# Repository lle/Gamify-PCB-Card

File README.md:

# Version 3: Added new game mode
## Change Logs
* Denser LED matrix
* Added Racing Game (hold "A" when powering on)
* Added LED animation/screensaver (hold "B" when powering on)
* Updated silkscreen and contact information

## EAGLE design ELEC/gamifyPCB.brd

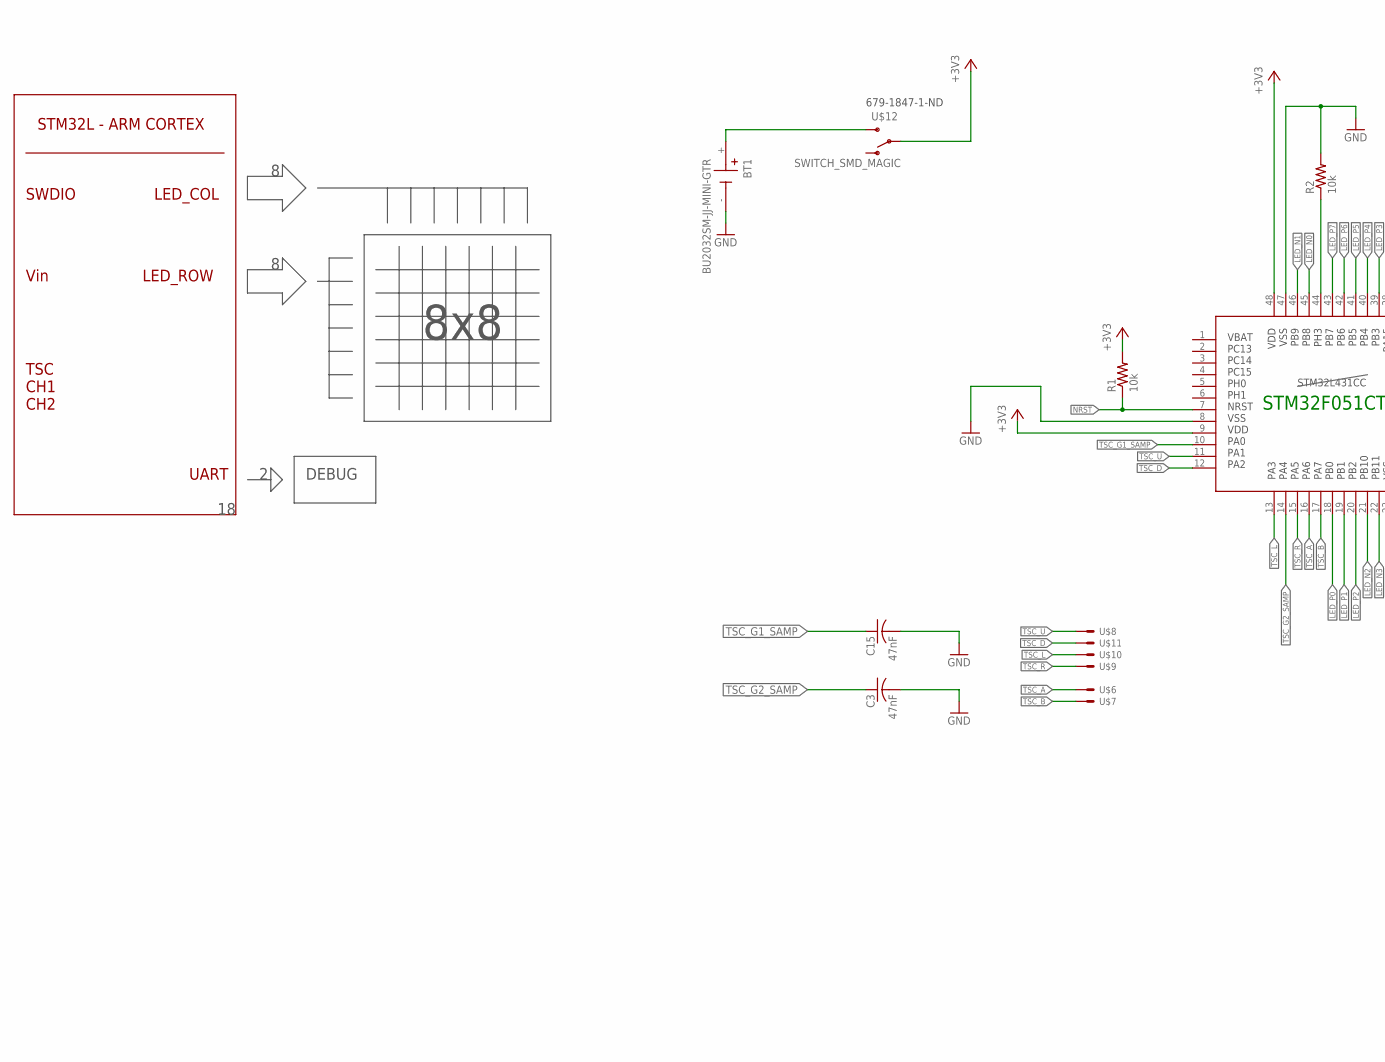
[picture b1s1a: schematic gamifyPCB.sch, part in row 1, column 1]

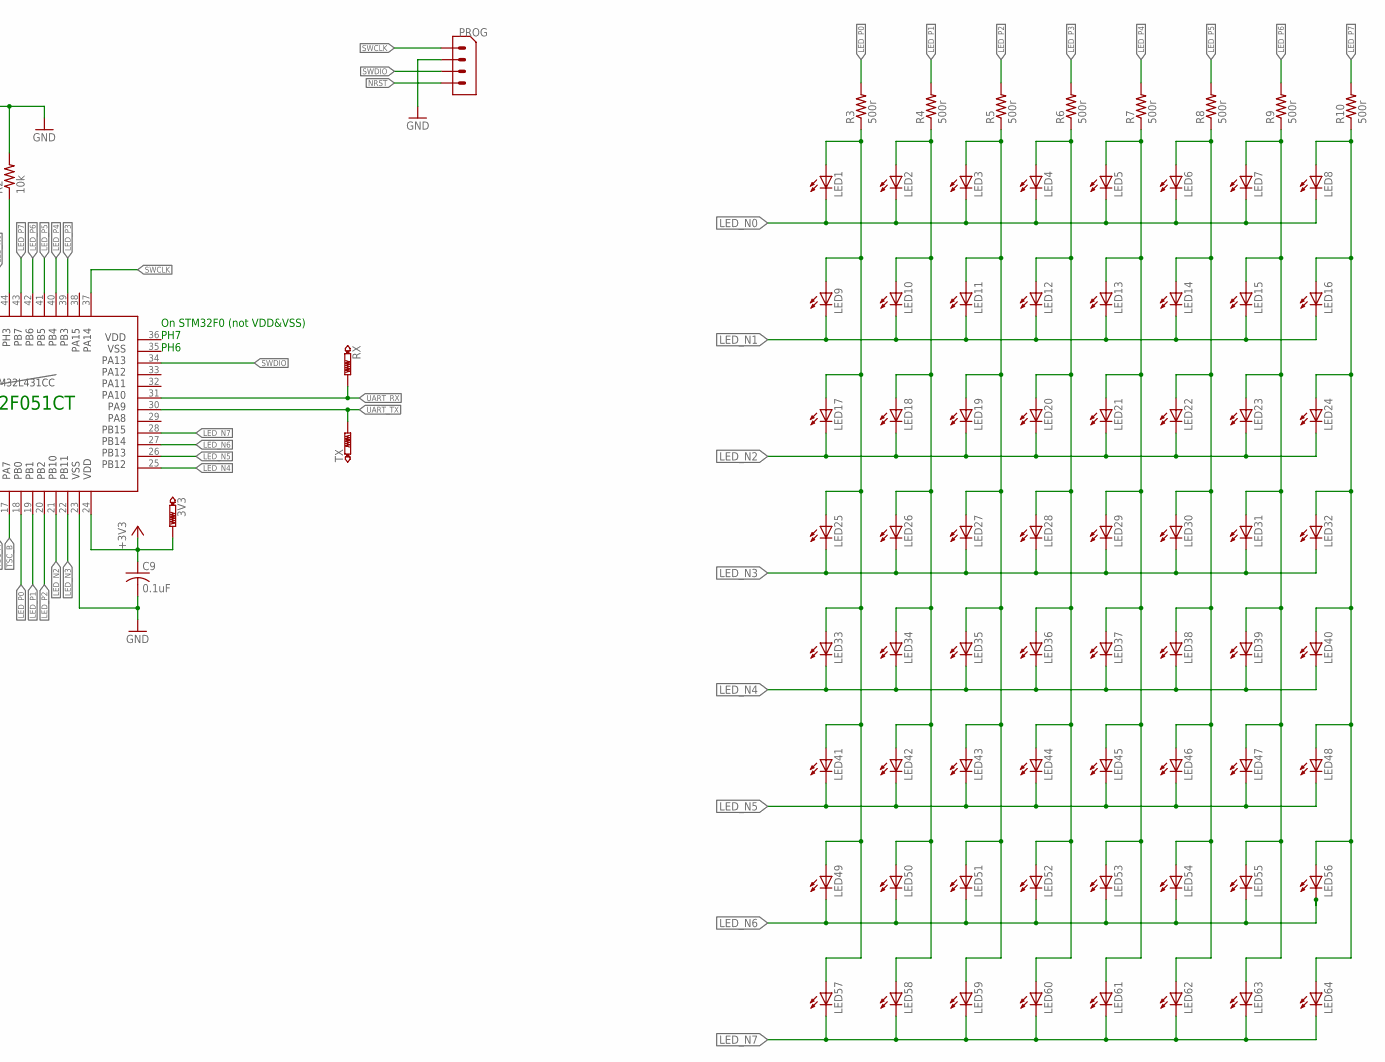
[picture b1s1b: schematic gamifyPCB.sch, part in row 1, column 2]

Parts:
3V3: PTR1B1,27; B1,27
BT1: BU2032SM-JJ-MINI-GTR; BAT_BU2032SM-JJ-MINI-GTR
C3, C15: 47nF; C0603
C9: 0.1uF; C0603
LED1, LED2, LED3, LED4, LED5, LED6, LED7, LED8, LED9, LED10, LED11, LED12, LED13, LED14, LED15, LED16, LED17, LED18, LED19, LED20, LED21, LED22, LED23, LED24, LED25, LED26, LED27, LED28, LED29, LED30, LED31, LED32, LED33, LED34, LED35, LED36, LED37, LED38, LED39, LED40, LED41, LED42, LED43, LED44, LED45, LED46, LED47, LED48, LED49, LED50, LED51, LED52, LED53, LED54, LED55, LED56, LED57, LED58, LED59, LED60, LED61, LED62, LED63, LED64: LEDCHIP-LED0603; CHIP-LED0603
PROG: 4-PIN-1.25MM
R1, R2: 10k; R0603
R3, R4, R5, R6, R7, R8, R9, R10: 500r; R0603
RX: PTR1B1,27; B1,27
TX: PTR1B1,27; B1,27
U$2: STM32L431CC; QFP50P900X900X160-48
U$6, U$7: CAP_BUTTON; CAPBUTTON
U$8, U$9, U$10, U$11: CAP_DPAD; DPAD
U$12: SWITCH_SMD_MAGIC; SWITCH_SMD_SUNKEN

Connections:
+3V3: 3V3.TP, C9.1, R1.2, U$2.9, U$2.24, U$2.48, U$12.2
GND: BT1.-, C3.2, C9.2, C15.2, PROG.P$3 (2), R2.2, U$2.8, U$2.23, U$2.47
LED_N0: LED1.C, LED2.C, LED3.C, LED4.C, LED5.C, LED6.C, LED7.C, LED8.C, U$2.45
LED_N1: LED9.C, LED10.C, LED11.C, LED12.C, LED13.C, LED14.C, LED15.C, LED16.C, U$2.46
LED_N2: LED17.C, LED18.C, LED19.C, LED20.C, LED21.C, LED22.C, LED23.C, LED24.C, U$2.21
LED_N3: LED25.C, LED26.C, LED27.C, LED28.C, LED29.C, LED30.C, LED31.C, LED32.C, U$2.22
LED_N4: LED33.C, LED34.C, LED35.C, LED36.C, LED37.C, LED38.C, LED39.C, LED40.C, U$2.25
LED_N5: LED41.C, LED42.C, LED43.C, LED44.C, LED45.C, LED46.C, LED47.C, LED48.C, U$2.26
LED_N6: LED49.C, LED50.C, LED51.C, LED52.C, LED53.C, LED54.C, LED55.C, LED56.C, U$2.27
LED_N7: LED57.C, LED58.C, LED59.C, LED60.C, LED61.C, LED62.C, LED63.C, LED64.C, U$2.28
LED_P0: R3.2, U$2.18
LED_P0B: LED1.A, LED9.A, LED17.A, LED25.A, LED33.A, LED41.A, LED49.A, LED57.A, R3.1
LED_P1: R4.2, U$2.19
LED_P1B: LED2.A, LED10.A, LED18.A, LED26.A, LED34.A, LED42.A, LED50.A, LED58.A, R4.1
LED_P2: R5.2, U$2.20
LED_P2B: LED3.A, LED11.A, LED19.A, LED27.A, LED35.A, LED43.A, LED51.A, LED59.A, R5.1
LED_P3: R6.2, U$2.39
LED_P3B: LED4.A, LED12.A, LED20.A, LED28.A, LED36.A, LED44.A, LED52.A, LED60.A, R6.1
LED_P4: R7.2, U$2.40
LED_P4B: LED5.A, LED13.A, LED21.A, LED29.A, LED37.A, LED45.A, LED53.A, LED61.A, R7.1
LED_P5: R8.2, U$2.41
LED_P5B: LED6.A, LED14.A, LED22.A, LED30.A, LED38.A, LED46.A, LED54.A, LED62.A, R8.1
LED_P6: R9.2, U$2.42
LED_P6B: LED7.A, LED15.A, LED23.A, LED31.A, LED39.A, LED47.A, LED55.A, LED63.A, R9.1
LED_P7: R10.2, U$2.43
LED_P7B: LED8.A, LED16.A, LED24.A, LED32.A, LED40.A, LED48.A, LED56.A, LED64.A, R10.1
unnamed: R2.1, U$2.44
unnamed: BT1.+, U$12.3 (S)
NRST: PROG.P$1 (4), R1.1, U$2.7
SWCLK: PROG.P$4 (1), U$2.37
SWDIO: PROG.P$2 (3), U$2.34
TSC_A: U$2.16, U$6.P$1, U$6.P$2
TSC_B: U$2.17, U$7.P$1, U$7.P$2
TSC_D: U$2.12, U$11.P$1
TSC_G1_SAMP: C15.1, U$2.10
TSC_G2_SAMP: C3.1, U$2.14
TSC_L: U$2.13, U$10.P$1
TSC_R: U$2.15, U$9.P$1
TSC_U: U$2.11, U$8.P$1
UART_RX: RX.TP, U$2.31
UART_TX: TX.TP, U$2.30

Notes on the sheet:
SWDIO
Vin
LED_COL
LED_ROW
TSC CH1 CH2
STM32L - ARM CORTEX
DEBUG
UART
8x8
679-1847-1-ND
STM32F051CT
On STM32F0 (not VDD&VSS) PH7 PH6

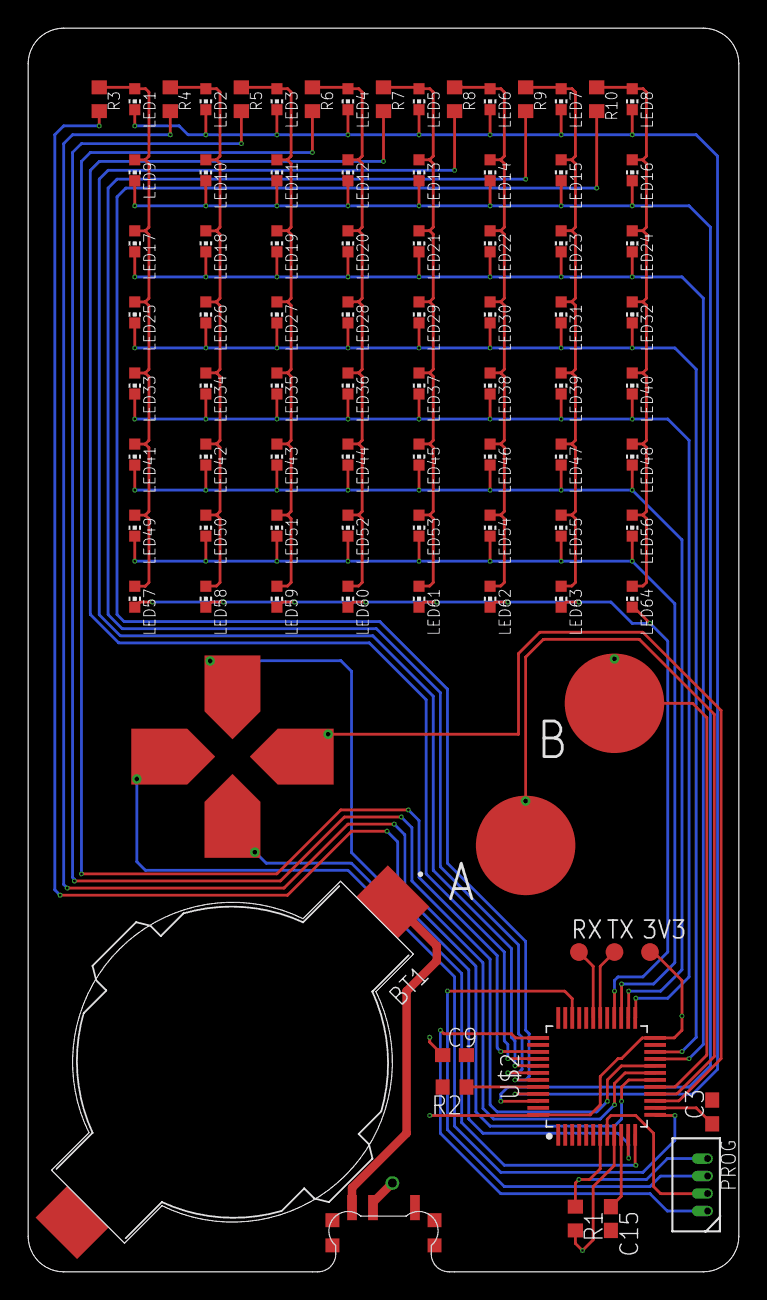
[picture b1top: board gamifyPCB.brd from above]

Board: 2 copper layers, 50.8 x 88.9 mm, 90 parts (0 on the bottom side), 41 nets.

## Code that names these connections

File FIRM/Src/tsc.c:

/**
  ******************************************************************************
  * File Name          : TSC.c
  * Description        : This file provides code for the configuration
  *                      of the TSC instances.
  ******************************************************************************
  * @attention
  *
  * <h2><center>&copy; Copyright (c) 2020 STMicroelectronics.
  * All rights reserved.</center></h2>
  *
  * This software component is licensed by ST under BSD 3-Clause license,
  * the "License"; You may not use this file except in compliance with the
  * License. You may obtain a copy of the License at:
  *                        opensource.org/licenses/BSD-3-Clause
  *
  ******************************************************************************
  */

/* Includes ------------------------------------------------------------------*/
#include "tsc.h"

/* USER CODE BEGIN 0 */

/* USER CODE END 0 */

TSC_HandleTypeDef htsc;

/* TSC init function */
void MX_TSC_Init(void)
{

  /** Configure the TSC peripheral 
  */
  htsc.Instance = TSC;
  htsc.Init.CTPulseHighLength = TSC_CTPH_8CYCLES;
  htsc.Init.CTPulseLowLength = TSC_CTPL_8CYCLES;
  htsc.Init.SpreadSpectrum = DISABLE;
  htsc.Init.SpreadSpectrumDeviation = 1;
  htsc.Init.SpreadSpectrumPrescaler = TSC_SS_PRESC_DIV1;
  htsc.Init.PulseGeneratorPrescaler = TSC_PG_PRESC_DIV2;
  htsc.Init.MaxCountValue = TSC_MCV_16383;
  htsc.Init.IODefaultMode = TSC_IODEF_OUT_PP_LOW;
  htsc.Init.SynchroPinPolarity = TSC_SYNC_POLARITY_FALLING;
  htsc.Init.AcquisitionMode = TSC_ACQ_MODE_NORMAL;
  htsc.Init.MaxCountInterrupt = ENABLE;
  htsc.Init.ChannelIOs = TSC_GROUP1_IO2|TSC_GROUP1_IO3|TSC_GROUP1_IO4|TSC_GROUP2_IO2
                    |TSC_GROUP2_IO3|TSC_GROUP2_IO4;
  htsc.Init.ShieldIOs = 0;
  htsc.Init.SamplingIOs = TSC_GROUP1_IO1|TSC_GROUP2_IO1;
  if (HAL_TSC_Init(&htsc) != HAL_OK)
  {
    Error_Handler();
  }

}

void HAL_TSC_MspInit(TSC_HandleTypeDef* tscHandle)
{

  GPIO_InitTypeDef GPIO_InitStruct = {0};
  if(tscHandle->Instance==TSC)
  {
  /* USER CODE BEGIN TSC_MspInit 0 */

  /* USER CODE END TSC_MspInit 0 */
    /* TSC clock enable */
    __HAL_RCC_TSC_CLK_ENABLE();
  
    __HAL_RCC_GPIOA_CLK_ENABLE();
    /**TSC GPIO Configuration    
    PA0     ------> TSC_G1_IO1
    PA1     ------> TSC_G1_IO2
    PA2     ------> TSC_G1_IO3
    PA3     ------> TSC_G1_IO4
    PA4     ------> TSC_G2_IO1
    PA5     ------> TSC_G2_IO2
    PA6     ------> TSC_G2_IO3
    PA7     ------> TSC_G2_IO4 
    */
    GPIO_InitStruct.Pin = GPIO_PIN_0|GPIO_PIN_4;
    GPIO_InitStruct.Mode = GPIO_MODE_AF_OD;
    GPIO_InitStruct.Pull = GPIO_NOPULL;
    GPIO_InitStruct.Speed = GPIO_SPEED_FREQ_LOW;
    GPIO_InitStruct.Alternate = GPIO_AF3_TSC;
    HAL_GPIO_Init(GPIOA, &GPIO_InitStruct);

    GPIO_InitStruct.Pin = TSC_UP_Pin|TSC_DN_Pin|TSC_L_Pin|TSC_R_Pin 
                          |TSC_A_Pin|TSC_B_Pin;
    GPIO_InitStruct.Mode = GPIO_MODE_AF_PP;
    GPIO_InitStruct.Pull = GPIO_NOPULL;
    GPIO_InitStruct.Speed = GPIO_SPEED_FREQ_LOW;
    GPIO_InitStruct.Alternate = GPIO_AF3_TSC;
    HAL_GPIO_Init(GPIOA, &GPIO_InitStruct);

    /* TSC interrupt Init */
    HAL_NVIC_SetPriority(TSC_IRQn, 0, 0);
    HAL_NVIC_EnableIRQ(TSC_IRQn);
  /* USER CODE BEGIN TSC_MspInit 1 */

  /* USER CODE END TSC_MspInit 1 */
  }
}

void HAL_TSC_MspDeInit(TSC_HandleTypeDef* tscHandle)
{

  if(tscHandle->Instance==TSC)
  {
  /* USER CODE BEGIN TSC_MspDeInit 0 */

  /* USER CODE END TSC_MspDeInit 0 */
    /* Peripheral clock disable */
    __HAL_RCC_TSC_CLK_DISABLE();
  
    /**TSC GPIO Configuration    
    PA0     ------> TSC_G1_IO1
    PA1     ------> TSC_G1_IO2
    PA2     ------> TSC_G1_IO3
    PA3     ------> TSC_G1_IO4
    PA4     ------> TSC_G2_IO1
    PA5     ------> TSC_G2_IO2
    PA6     ------> TSC_G2_IO3
    PA7     ------> TSC_G2_IO4 
    */
    HAL_GPIO_DeInit(GPIOA, GPIO_PIN_0|TSC_UP_Pin|TSC_DN_Pin|TSC_L_Pin 
                          |GPIO_PIN_4|TSC_R_Pin|TSC_A_Pin|TSC_B_Pin);

    /* TSC interrupt Deinit */
    HAL_NVIC_DisableIRQ(TSC_IRQn);
  /* USER CODE BEGIN TSC_MspDeInit 1 */

  /* USER CODE END TSC_MspDeInit 1 */
  }
} 

/* USER CODE BEGIN 1 */

/* USER CODE END 1 */

/************************ (C) COPYRIGHT STMicroelectronics *****END OF FILE****/

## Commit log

2020-02-10 Initial Push for V1
    EagleCAD design file for the gamified PCB Business Card.
2020-08-09 created readme
2021-10-26 Added BOM
2022-09-19 Added new branch for V2
    Removed captouch and replaced with physical button.
    Added pseudo random seed using ADC input floating pin.
    Starting point of snake/apple is now randomized
2022-09-19 Updated V2 readme
2022-09-20 Updated youtube link
2022-09-20 Added header
2022-09-20 change header
2024-06-28 Rename files and prepare for editing
2024-07-09 Gerbers ready for production
    - Tighter matrix, LED at 45 degrees
    - New silkscreen
2024-07-23 Added different modes
    - added raceCar games (imported from my SAO-defcon32) (hold A during boot)
    - added animation only mode (hold B during boot)
2026-06-18 remove obsolete
